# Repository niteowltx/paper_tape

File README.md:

A Paper Tape Reader for ancient ASR33 class paper tapes.

	Paper is 1" wide with 9 holes on 0.1" centers.  Rows are also 0.1" apart.
	Data holes are 0.072" diameter, sprocket hole is 0.046" diameter
	Sprocket is small so it works as a strobe for the data

	Paper Tape layout:
		D0 D1 D2 St D3 D4 D5 D6 D7

Hardware:
	3D printed paper tape guide (top and bottom)

	top board: IR LED array (OSRAM SFH-4949), pullup resistor network (2K ohms)

	bottom board: Photo diode array (OSRAM BPX89), pulldown resistor network (1K ohms)

	process board: Adafruit Metro Mini, USB power and serial in/out

	Top and Bottom boards are identical, just flipped and populated differently.  Top
		board (IR LED) only connects +5 and Gnd.

	Signal cleanup between the Photodiode array and the Arduino are not necessary
		since the ATmega328 has Schmitt triggers built in.

	Photodiode Array to Arduino wiring:

		D0 -> PB0 -> Digital Pin 8
		D1 -> PB1 -> Digital Pin 9
		D2 -> PB2 -> Digital Pin 10
		D3 -> PB3 -> Digital Pin 11
		D4 -> PB4 -> Digital Pin 12
		D5 -> PD5 -> Digital Pin 5
		D6 -> PD6 -> Digital Pin 6
		D7 -> PD7 -> Digital Pin 7
		St -> PD2 -> Digital Pin 2 (INT0)

		To read all 8 bits in 2 reads from I/O Ports:
			byte = (PINB & 0x1F) | (PIND & 0xE0);

Software:
	Strobe generates interrupt on Arduino which reads byte and puts it in a FIFO.
		FIFO is 1000 bytes deep to allow for irregularites in serial output and
		the speed at which the loop() function is called.

	Main loop pulls bytes from FIFO and sends them via USB serial to host.

	Bytes are printed in HEX and a 2-character ASCII representaion of the lower 7-bits

	Serial output is set to 115200 which is fast enough for 96 ft/sec when the raw bytes
		from the tape are just sent over the serial port.  Printing bytes with a little formatting
		in HEX and printable ASCII reduces this to 16 ft/sec.

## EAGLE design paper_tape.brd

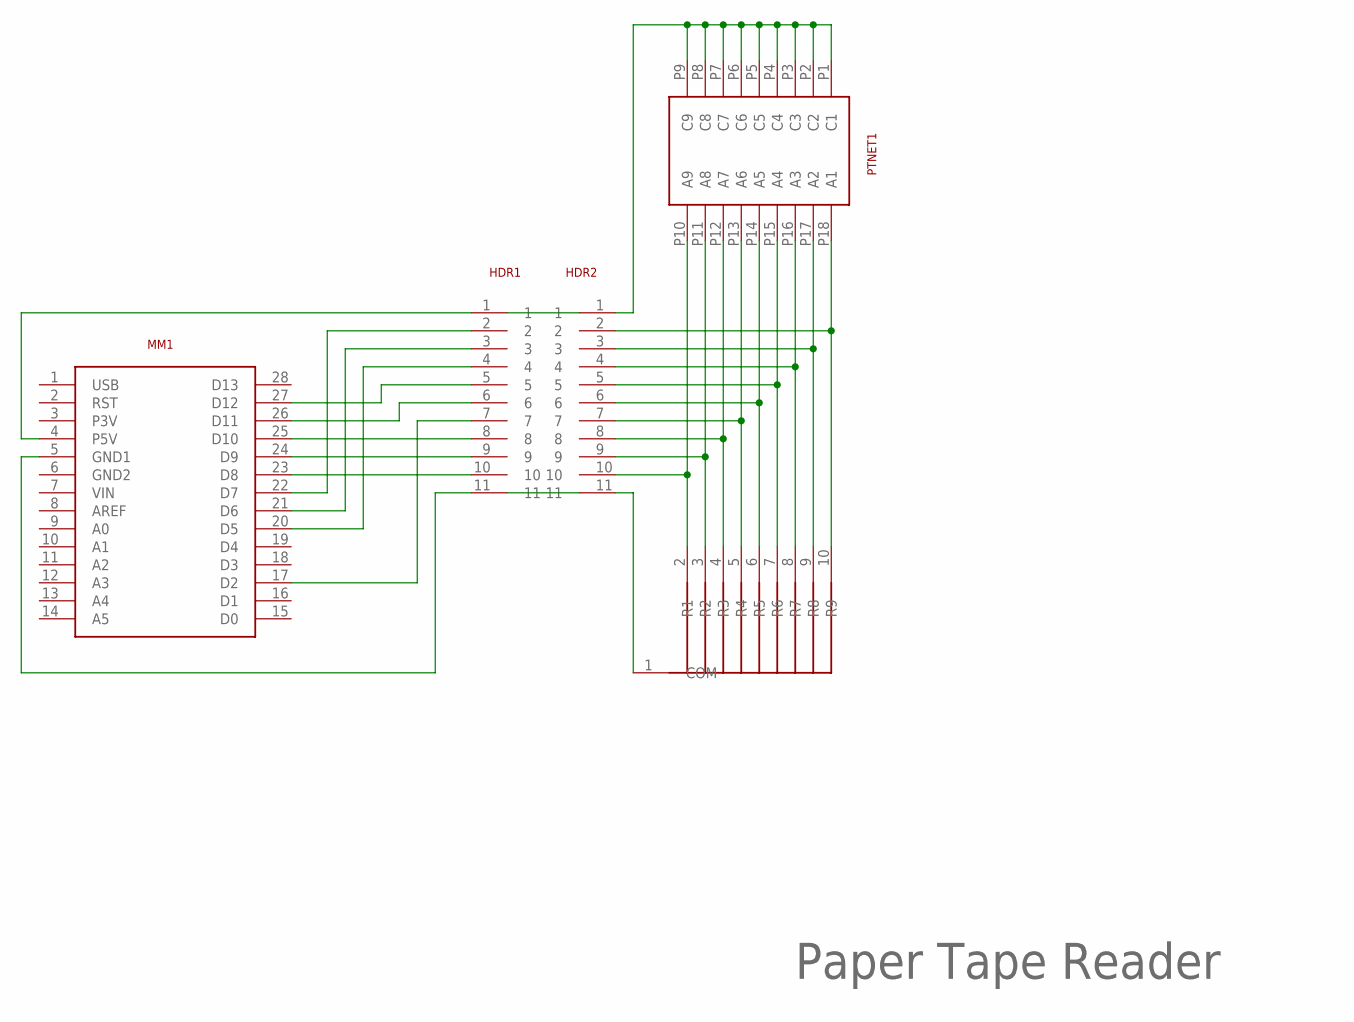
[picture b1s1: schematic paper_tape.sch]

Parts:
HDR1, HDR2: HEADER; SIP11
MM1: METRO_MINI; DIP28
PTNET1: PBX89; DIP18N
RN1: 1k; SIP10

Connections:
GND: HDR1.11, HDR2.11, MM1.5 (GND1), RN1.1 (COM)
unnamed: HDR1.7, MM1.17 (D2)
unnamed: HDR1.6, MM1.26 (D11)
unnamed: HDR1.5, MM1.27 (D12)
unnamed: HDR1.4, MM1.20 (D5)
unnamed: HDR1.3, MM1.21 (D6)
unnamed: HDR1.2, MM1.22 (D7)
unnamed: HDR1.1, MM1.4 (P5V)
unnamed: HDR1.8, MM1.25 (D10)
unnamed: HDR1.9, MM1.24 (D9)
unnamed: HDR1.10, MM1.23 (D8)
P5V: HDR2.1, PTNET1.P1 (C1), PTNET1.P2 (C2), PTNET1.P3 (C3), PTNET1.P4 (C4), PTNET1.P5 (C5), PTNET1.P6 (C6), PTNET1.P7 (C7), PTNET1.P8 (C8), PTNET1.P9 (C9)
PT_D0: HDR2.10, PTNET1.P10 (A9), RN1.2 (R1)
PT_D1: HDR2.9, PTNET1.P11 (A8), RN1.3 (R2)
PT_D2: HDR2.8, PTNET1.P12 (A7), RN1.4 (R3)
PT_D3: HDR2.6, PTNET1.P14 (A5), RN1.6 (R5)
PT_D4: HDR2.5, PTNET1.P15 (A4), RN1.7 (R6)
PT_D5: HDR2.4, PTNET1.P16 (A3), RN1.8 (R7)
PT_D6: HDR2.3, PTNET1.P17 (A2), RN1.9 (R8)
PT_D7: HDR2.2, PTNET1.P18 (A1), RN1.10 (R9)
PT_STROBE: HDR2.7, PTNET1.P13 (A6), RN1.5 (R4)

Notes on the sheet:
Paper Tape Reader

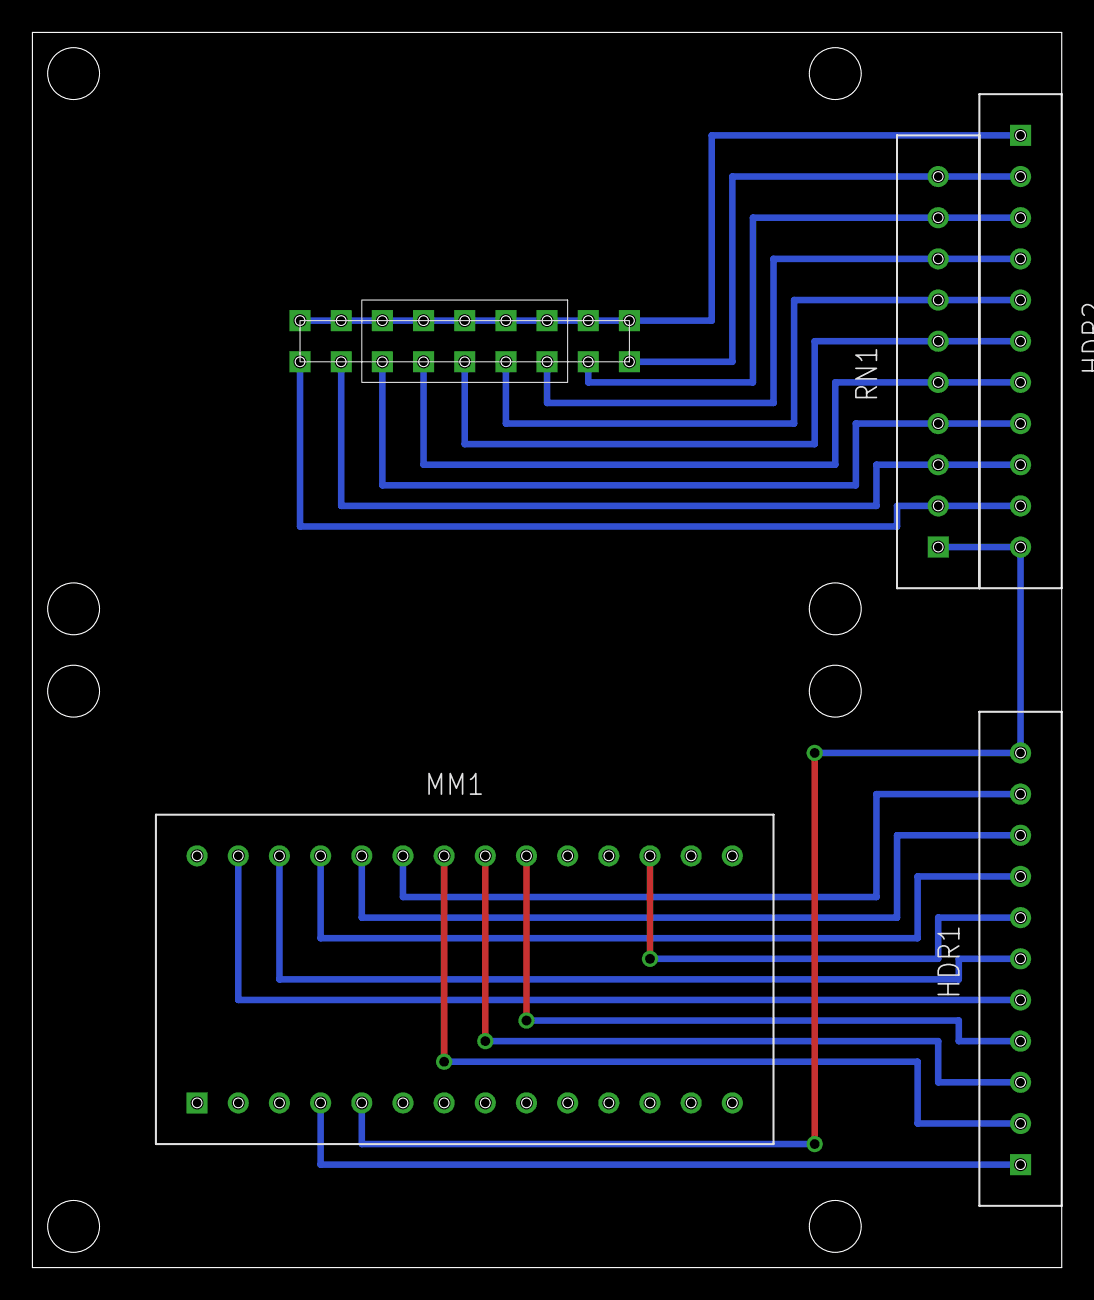
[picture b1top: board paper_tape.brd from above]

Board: 2 copper layers, 63.5 x 76.2 mm, 5 parts (0 on the bottom side), 21 nets.

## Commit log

2022-12-17 add doc directory
2022-12-18 rename arduino file to match the rest
